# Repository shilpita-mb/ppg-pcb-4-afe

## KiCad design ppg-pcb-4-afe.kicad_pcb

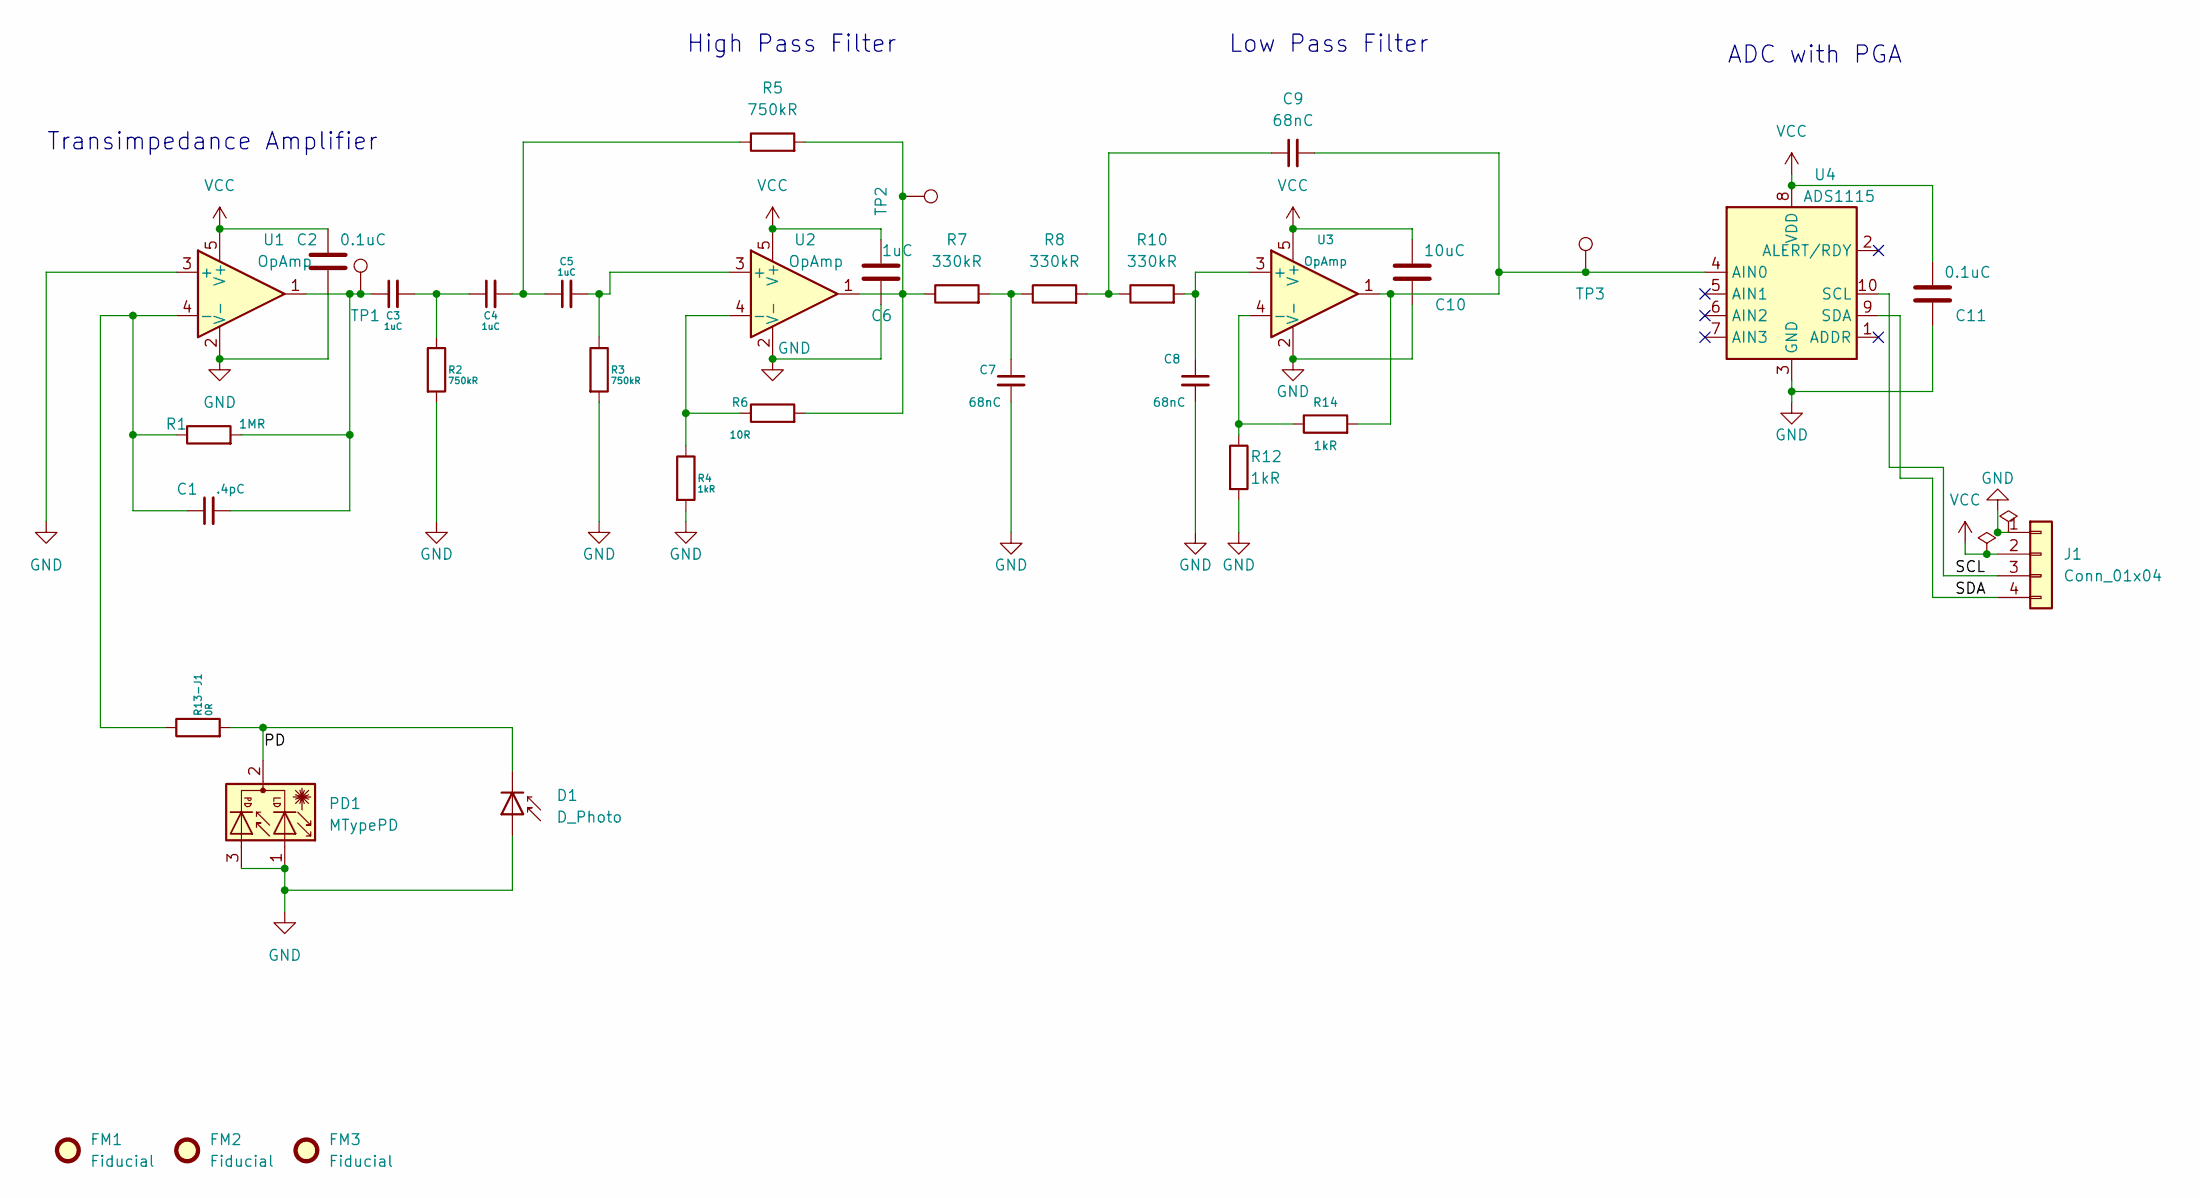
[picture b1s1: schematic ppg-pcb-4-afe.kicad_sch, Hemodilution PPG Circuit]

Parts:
C1: .4pC; C_0603_1608Metric
C2, C11: 0.1uC; C_0603_1608Metric
C3, C4, C5, C6: 1uC; C_0603_1608Metric
C7, C8, C9: 68nC; C_0603_1608Metric
C10: 10uC; C_0603_1608Metric
D1: D_Photo; LED_1206_3216Metric
FM1, FM2, FM3: Fiducial; Fiducial_1mm_Mask2mm
J1: Conn_01x04; PinSocket_1x04_P2.54mm_Vertical
PD1: MTypePD; FGA21
R1: 1MR; R_0805_2012Metric
R2, R3, R5: 750kR; R_0603_1608Metric
R4, R12, R14: 1kR; R_0603_1608Metric
R6: 10R; R_0603_1608Metric
R7, R8, R10: 330kR; R_0603_1608Metric
R13-J1: 0R; R_0603_1608Metric
TP1, TP2, TP3: TestPoint; TestPoint_Keystone_5000-5004_Miniature
U1, U2, U3: OpAmp; SOT-23-5
U4: ADS1115; TSSOP-10_3x3mm_P0.5mm

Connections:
/PD: D1.1 (K), PD1.2, R13-J1.2
/SCL: J1.3, U4.10 (SCL)
/SDA: J1.4, U4.9 (SDA)
GND: C2.2, C6.2, C7.2, C8.2, C10.2, C11.2, D1.2 (A), J1.1, PD1.1, PD1.3, R2.2, R3.2, R4.2, R12.2, U1.2 (V-), U1.3 (+), U2.2 (V-), U3.2 (V-), U4.3 (GND)
unnamed: C1.2, C3.1, R1.2, TP1.1, U1.1
unnamed: C3.2, C4.1, R2.1
unnamed: C4.2, C5.1, R5.1
unnamed: C7.1, R7.2, R8.1
unnamed: C9.1, R8.2, R10.1
unnamed: R5.2, R6.2, R7.1, TP2.1, U2.1
unnamed: C1.1, R1.1, R13-J1.1, U1.4 (-)
unnamed: C5.2, R3.1, U2.3 (+)
unnamed: R4.1, R6.1, U2.4 (-)
unnamed: C8.1, R10.2, U3.3 (+)
unnamed: R12.1, R14.1, U3.4 (-)
unnamed: C9.2, R14.2, TP3.1, U3.1, U4.4 (AIN0)
VCC: C2.1, C6.1, C10.1, C11.1, J1.2, U1.5 (V+), U2.5 (V+), U3.5 (V+), U4.8 (VDD)

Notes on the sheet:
High Pass Filter
ADC with PGA
Low Pass Filter
Transimpedance Amplifier

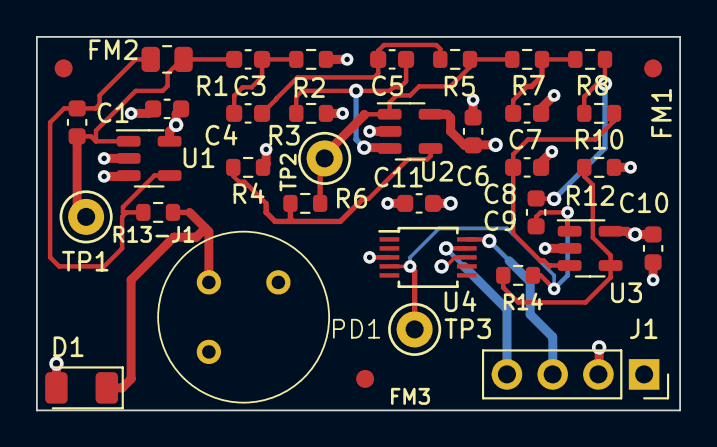
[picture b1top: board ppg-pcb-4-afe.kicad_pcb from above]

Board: 4 copper layers, 35.7 x 20.8 mm, 36 parts (0 on the bottom side), 17 nets.

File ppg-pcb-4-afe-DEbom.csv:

#,Reference,Qty,Value,Footprint,DNP,DE Purchase,Notes,Link
1,C1,1,.4pC,Capacitor_SMD:C_0603_1608Metric,,Yes,,
2,"C2, C11",2,0.1uC,Capacitor_SMD:C_0603_1608Metric,,Yes,,
3,"C3, C4, C5, C6",4,1uC,Capacitor_SMD:C_0603_1608Metric,,Yes,,
4,"C7, C8, C9",3,68nC,Capacitor_SMD:C_0603_1608Metric,,Yes,,
5,C10,1,10uC,Capacitor_SMD:C_0603_1608Metric,,Yes,,
6,D1,1,D_Photo,LED_SMD:LED_1206_3216Metric,,self solder,,
7,"FM1, FM2, FM3",3,Fiducial,Fiducial:Fiducial_1mm_Mask2mm,,N/A,,
8,J1,1,Conn_01x04,Connector_PinSocket_2.54mm:PinSocket_1x04_P2.54mm_Vertical,,Yes,Photo has 10 pins but datasheet is 4,https://www.mouser.com/ProductDetail/Harwin/M20-7820446?qs=v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
9,PD1,1,MTypePD,ppg:FGA21,,self solder,,
10,R1,1,1MR,Resistor_SMD:R_0805_2012Metric,,Yes,,
11,"R2, R3, R5",3,750kR,Resistor_SMD:R_0603_1608Metric,,Yes,,
12,"R4, R12, R14",3,1kR,Resistor_SMD:R_0603_1608Metric,,Yes,,
13,R6,1,10R,Resistor_SMD:R_0603_1608Metric,,Yes,,
14,"R7, R8, R10",3,330kR,Resistor_SMD:R_0603_1608Metric,,Yes,,
15,R13-J1,1,0R,Resistor_SMD:R_0603_1608Metric,,Yes,,
16,"TP1, TP2, TP3",3,TestPoint,TestPoint:TestPoint_Keystone_5000-5004_Miniature,,Yes,,
17,"U1, U2, U3",3,OpAmp,Package_TO_SOT_SMD:SOT-23-5,,Provided by O Lab,,
18,U4,1,ADS1115,Package_SO:TSSOP-10_3x3mm_P0.5mm,,Provided by O Lab,,

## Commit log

2025-08-05 All files uploaded, initial commit
2025-08-06 Removed colors from nets in copper layer
